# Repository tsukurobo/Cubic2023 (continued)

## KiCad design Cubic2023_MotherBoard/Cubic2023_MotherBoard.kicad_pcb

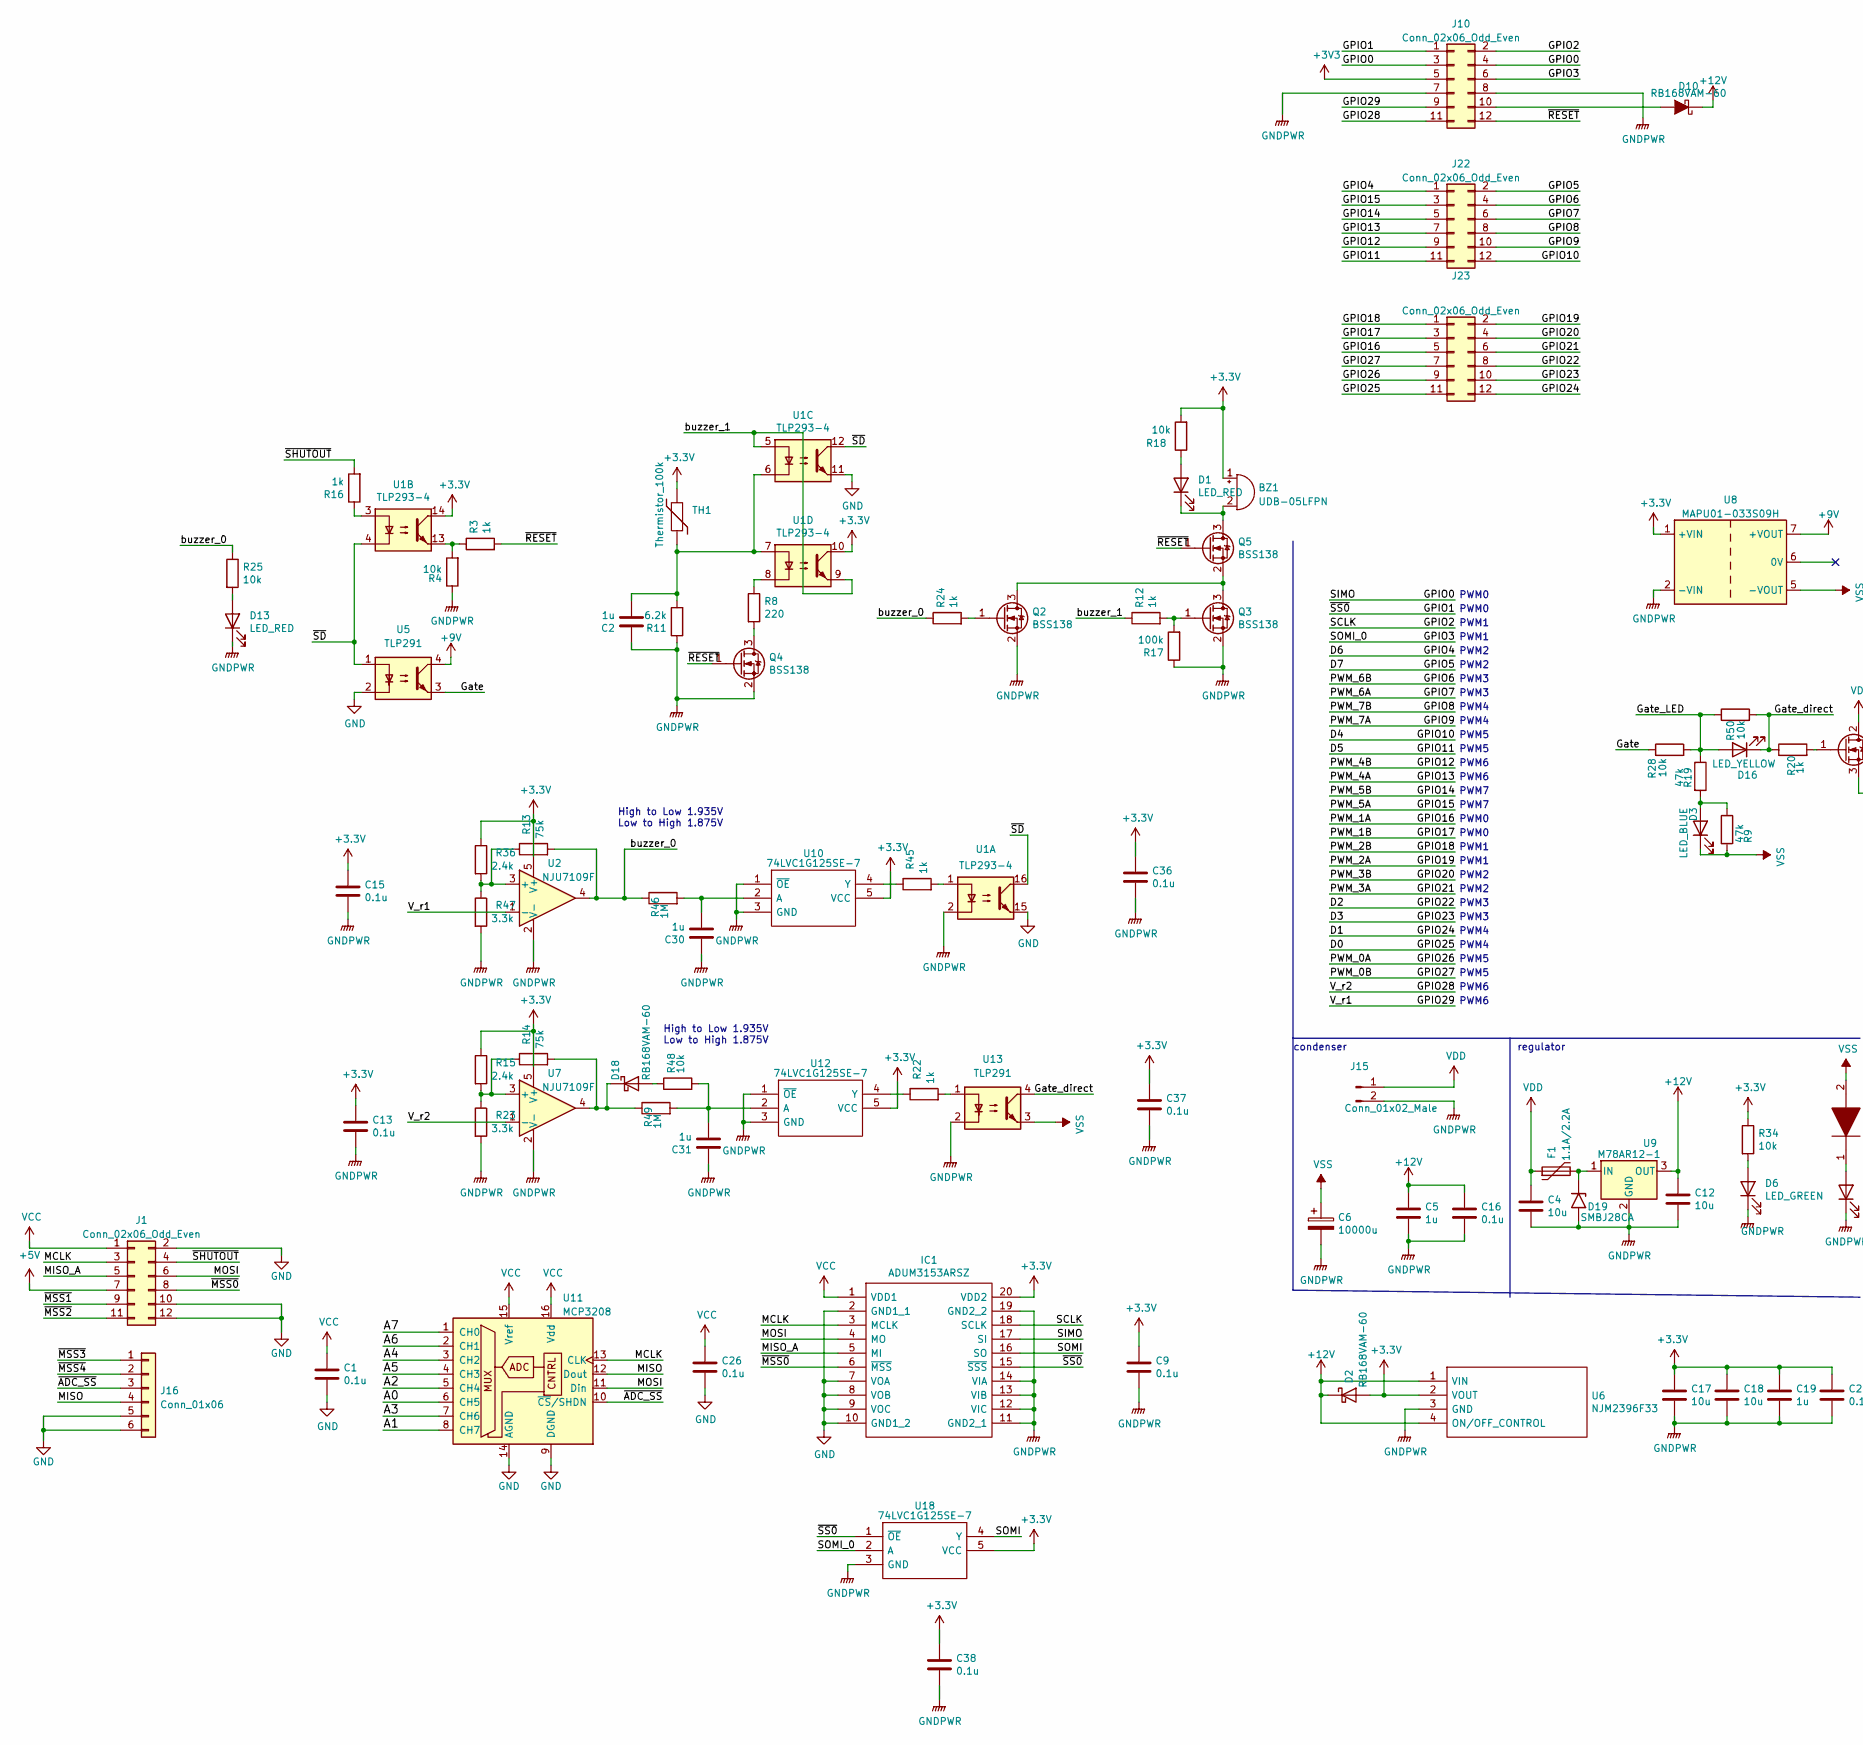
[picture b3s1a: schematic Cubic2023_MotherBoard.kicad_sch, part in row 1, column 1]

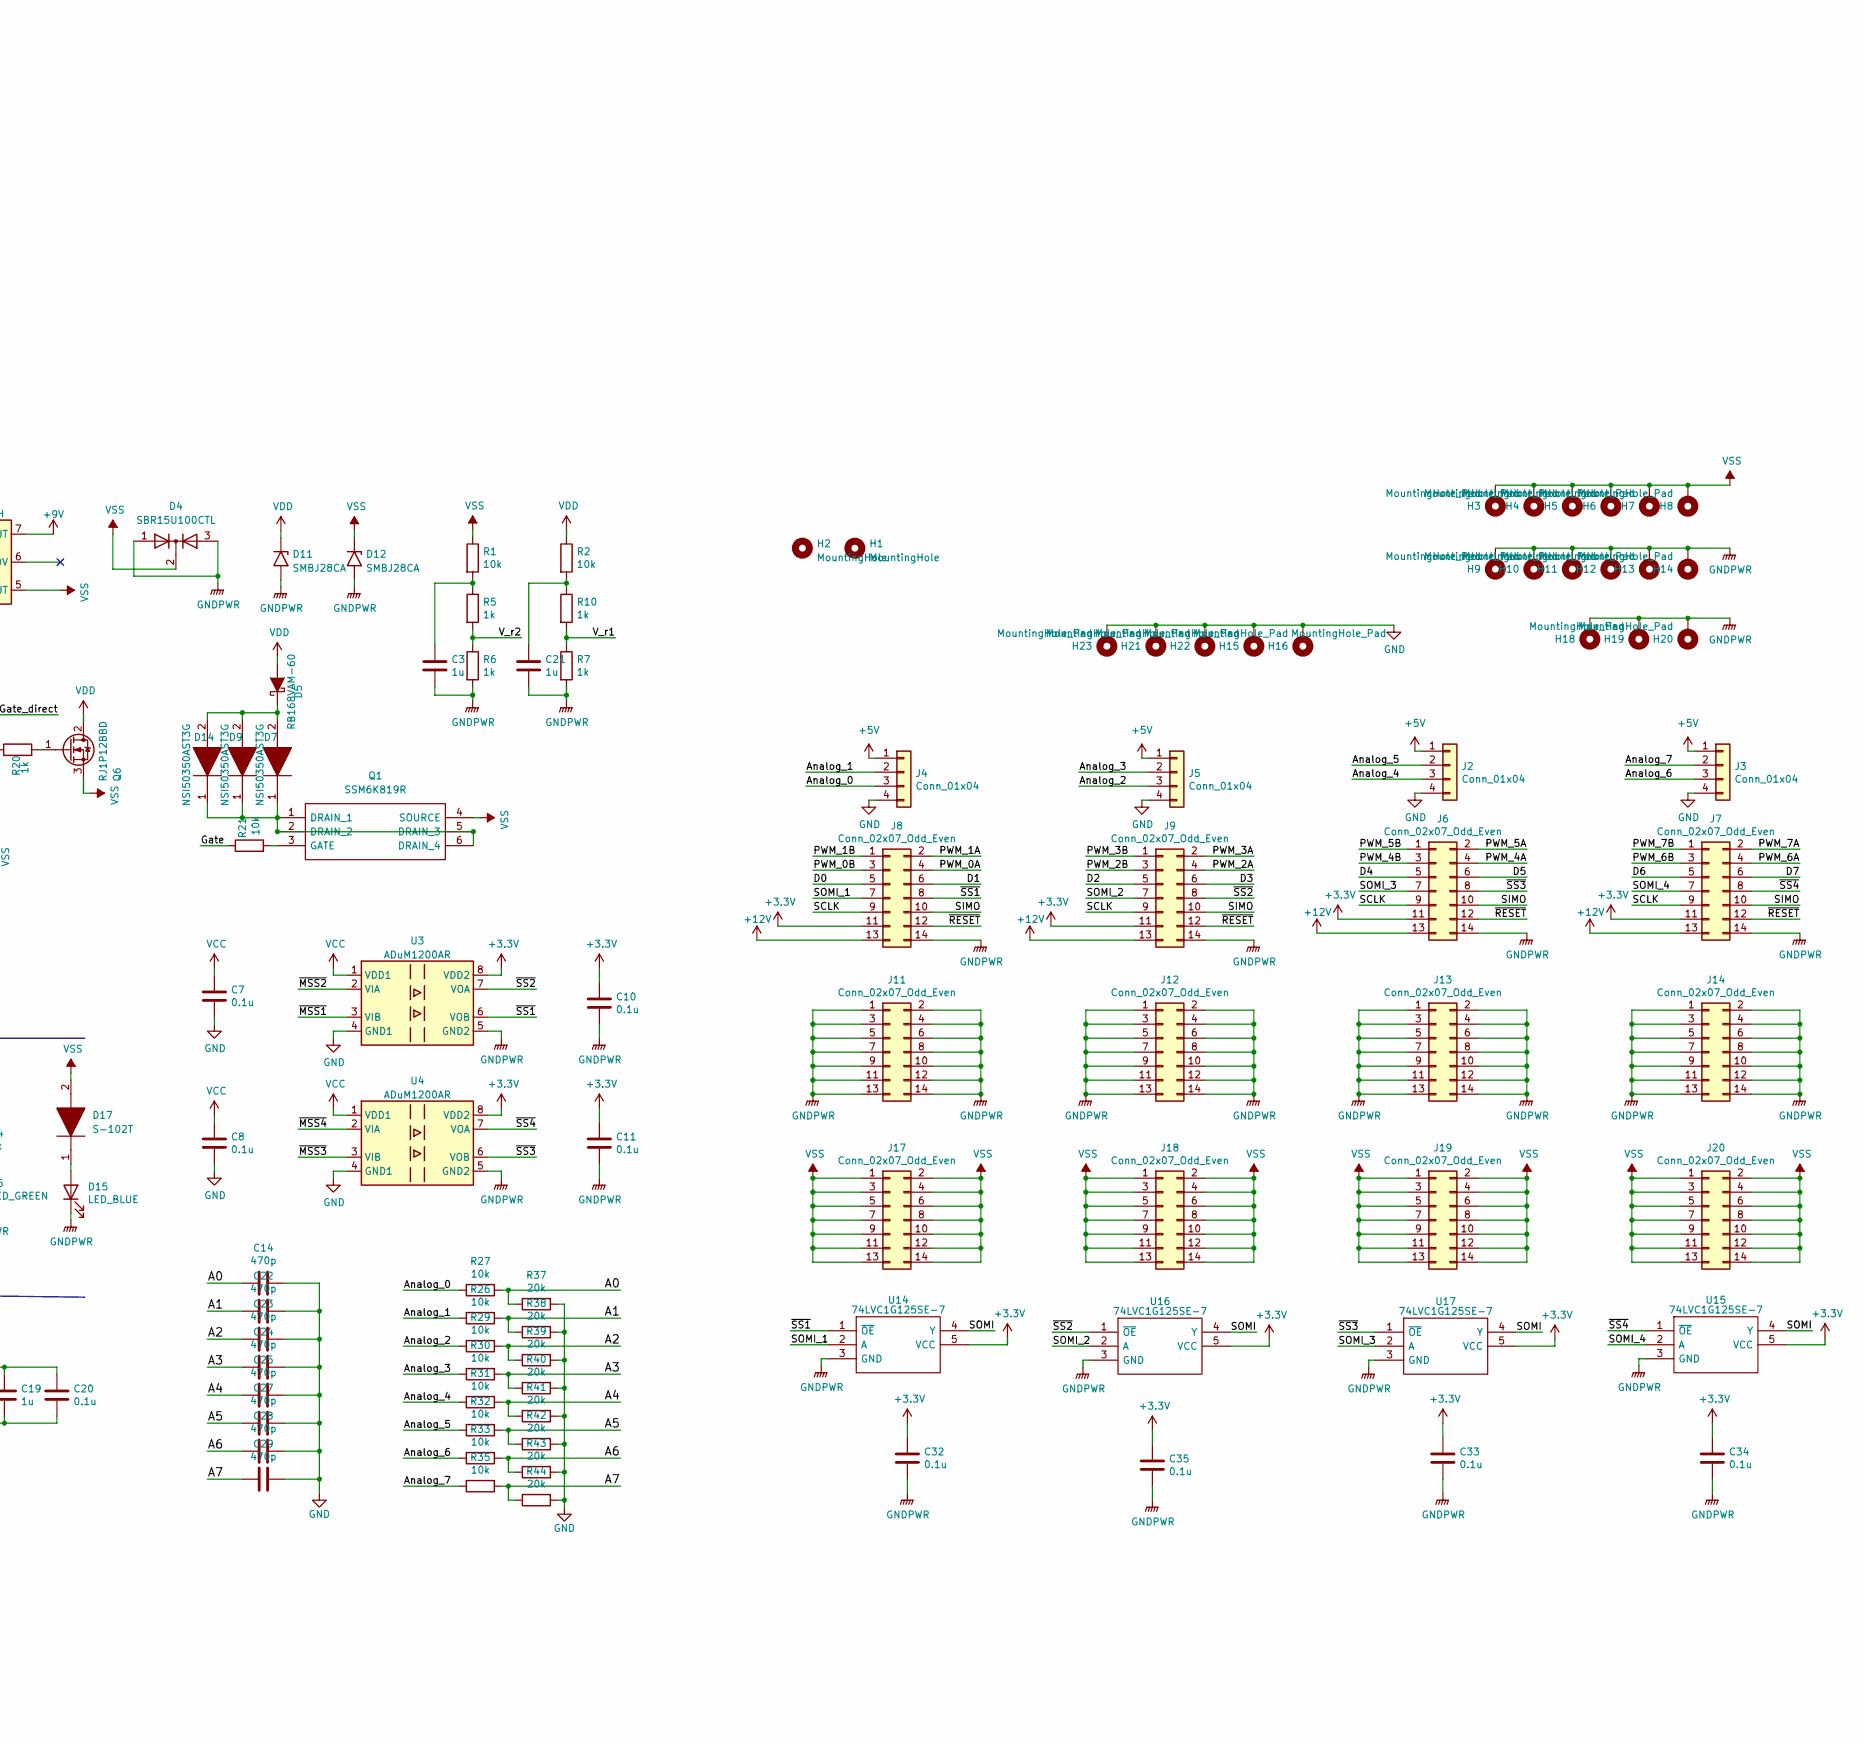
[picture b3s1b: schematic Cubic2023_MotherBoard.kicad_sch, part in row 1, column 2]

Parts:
BZ1: UDB-05LFPN; Buzzer_12x9.5RM7.6
C1, C7, C8, C9, C10, C11, C13, C15, C16, C20, C26, C32, C33, C34, C35, C36, C37, C38: 0.1u; C_0402_1005Metric_Pad0.74x0.62mm_HandSolder; LCSC C307331
C2, C3, C5, C19, C21, C30, C31: 1u; C_0603_1608Metric; LCSC C15849
C4, C12, C17, C18: 10u; C_1206_3216Metric; LCSC C13585
C6: 10000u; CP_Radial_D25.0mm_P10.00mm_SnapIn
C14, C22, C23, C24, C25, C27, C28, C29: 470p; C_0603_1608Metric; LCSC C1620
D1, D13: LED_RED; LED_0603_1608Metric_Pad1.05x0.95mm_HandSolder; LCSC C2286
D2, D5, D10, D18: RB168VAM-60; CUHS20S40H3F
D3, D15: LED_BLUE; LED_0603_1608Metric_Pad1.05x0.95mm_HandSolder; LCSC C72041
D4: SBR15U100CTL; TO-252-2
D6: LED_GREEN; LED_0603_1608Metric_Pad1.05x0.95mm_HandSolder; LCSC C72043
D7, D9, D14: NSI50350AST3G; DIOM7958X256N; Manufacturer_Part_Number NSI50350AST3G; Mouser Part Number 863-NSI50350AST3G
D11, D12, D19: SMBJ28CA; D_SMB
D16: LED_YELLOW; LED_0603_1608Metric_Pad1.05x0.95mm_HandSolder; LCSC C72038
D17: S-102T; SODFL3516X70N; Manufacturer_Part_Number S-102T; Mouser Part Number 954-S-102T
F1: 1.1A/2.2A; Fuse_BelFuse_0ZRE0016FF_L9.9mm_W3.8mm
H1, H2: MountingHole; MountingHole_3.2mm_M3
H3, H4, H5, H6, H7, H8, H9, H10, H11, H12, H13, H14, H15, H16, H18, H19, H20, H21, H22, H23: MountingHole_Pad; MountingHole_2.2mm_M2_DIN965_Pad
IC1: ADUM3153ARSZ; ADUM3153; Manufacturer_Part_Number ADUM3153ARSZ; Mouser Part Number 584-ADUM3153ARSZ
J1: Conn_02x06_Odd_Even; PinSocket_2x06_P2.54mm_Vertical
J2, J3, J4, J5: Conn_01x04; PinSocket_1x04_P2.54mm_Vertical
J6, J7, J8, J9, J11, J12, J13, J14, J17, J18, J19, J20: Conn_02x07_Odd_Even; PinSocket_2x07_P2.54mm_Vertical
J10, J22, J23: Conn_02x06_Odd_Even; PinHeader_2x06_P1.27mm_Vertical
J15: Conn_01x02_Male; T_plug_male_diagonal
J16: Conn_01x06; PinSocket_1x06_P2.54mm_Vertical
Q1: SSM6K819R; SOTFL95P280X88-6N; Manufacturer_Part_Number SSM6K819R; Mouser Part Number N/A
Q2, Q3, Q4, Q5: BSS138; SOT-23
Q6: RJ1P12BBD; TO-263-2
R1, R2, R4, R18, R21, R25, R26, R27, R28, R29, R30, R31, R32, R33, R34, R35, R48, R50: 10k; R_0603_1608Metric; LCSC C25804
R3, R5, R6, R7, R10, R12, R16, R20, R22, R24, R45: 1k; R_0603_1608Metric; LCSC C21190
R8: 220; R_0603_1608Metric; LCSC C22962
R9, R19: 47k; R_0603_1608Metric; LCSC C25819
R11: 6.2k; R_0603_1608Metric; LCSC C25804
R13, R14: 75k; R_0603_1608Metric; LCSC C23242
R15, R36: 2.4k; R_0603_1608Metric; LCSC C22940
R17: 100k; R_0603_1608Metric; LCSC C25803
R23, R47: 3.3k; R_0603_1608Metric; LCSC C22978
R37, R38, R39, R40, R41, R42, R43, R44: 20k; R_0603_1608Metric; LCSC C4184
R46, R49: 1M; R_0603_1608Metric; LCSC C22935
TH1: Thermistor_100k; R_0603_1608Metric
U1: TLP293-4; SO-16_5.3x10.2mm_P1.27mm
U2, U7: NJU7109F; SOT-23-5
U3, U4: ADuM1200AR; SOIC-8_3.9x4.9mm_P1.27mm
U5, U13: TLP291; SOIC-4_4.55x2.6mm_P1.27mm
U6: NJM2396F33; TO-220-4_Horizontal_TabUp; Manufacturer_Part_Number NJM2396F33; Mouser Part Number 513-NJM2396F33
U8: MAPU01-033S09H; MAPU01
U9: M78AR12-1; TO-220-3_Vertical
U10, U12, U14, U15, U16, U17, U18: 74LVC1G125SE-7; SOT-353_SC-70-5; Manufacturer_Part_Number 74LVC1G125SE-7; Mouser Part Number 621-74LVC1G125SE-7
U11: MCP3208; SOIC-16_3.9x9.9mm_P1.27mm

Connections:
+5V: J1.7, J2.1, J3.1, J4.1, J5.1
+9V: U5.4, U8.7 (+VOUT)
+12V: C5.1, C12.1, C16.1, D2.1 (K), D10.1 (K), J6.13, J7.13, J8.13, J9.13, U6.1 (VIN), U6.4 (ON/OFF_CONTROL), U9.3 (OUT)
/A0: C14.1, R27.1, R37.2, U11.6 (CH5)
/A1: C22.1, R26.1, R38.2, U11.8 (CH7)
/A2: C23.1, R29.1, R39.2, U11.5 (CH4)
/A3: C24.1, R30.1, R40.2, U11.7 (CH6)
/A4: C25.1, R31.1, R41.2, U11.3 (CH2)
/A5: C27.1, R32.1, R42.2, U11.4 (CH3)
/A6: C28.1, R33.1, R43.2, U11.2 (CH1)
/A7: C29.1, R35.1, R44.2, U11.1 (CH0)
/Analog_0: J4.3, R27.2
/Analog_1: J4.2, R26.2
/Analog_2: J5.3, R29.2
/Analog_3: J5.2, R30.2
/Analog_4: J2.3, R31.2
/Analog_5: J2.2, R32.2
/Analog_6: J3.3, R33.2
/Analog_7: J3.2, R35.2
/D0: J8.5, J23.11
/D1: J8.6, J23.12
/D2: J9.5, J23.8
/D3: J9.6, J23.10
/D4: J6.5, J22.12
/D5: J6.6, J22.11
/D6: J7.5, J22.1
/D7: J7.6, J22.2
/GPIO0: IC1.17 (SI), J6.10, J7.10, J8.10, J9.10, J10.3, J10.4
/GPIO1: IC1.15 (~SSS), J10.1, U18.1 (~OE)
/GPIO2: IC1.18 (SCLK), J6.9, J7.9, J8.9, J9.9, J10.2
/GPIO3: J10.6, U18.2 (A)
/GPIO6: J7.3, J22.4
/GPIO7: J7.4, J22.6
/GPIO8: J7.1, J22.8
/GPIO9: J7.2, J22.10
/GPIO12: J6.3, J22.9
/GPIO13: J6.4, J22.7
/GPIO14: J6.1, J22.5
/GPIO15: J6.2, J22.3
/GPIO16: J8.2, J23.5
/GPIO17: J8.1, J23.3
/GPIO18: J9.3, J23.1
/GPIO19: J9.4, J23.2
/GPIO20: J9.1, J23.4
/GPIO21: J9.2, J23.6
/GPIO26: J8.4, J23.9
/GPIO27: J8.3, J23.7
/GPIO28: J10.11, R5.2, R6.1, U7.1 (-)
/GPIO29: J10.9, R7.1, R10.2, U2.1 (-)
/Gate: R21.1, R28.1, U5.3
/Gate_LED: D16.2 (A), R19.1, R28.2, R50.1
/Gate_direct: D16.1 (K), R20.1, R50.2, U13.4
/MCLK: IC1.3 (MCLK), J1.3, U11.13 (CLK)
/MISO: J16.4, U11.12 (Dout)
/MISO_A: IC1.5 (MI), J1.5
/MOSI: IC1.4 (MO), J1.6, U11.11 (Din)
/SOMI: IC1.16 (SO), U14.4 (Y), U15.4 (Y), U16.4 (Y), U17.4 (Y), U18.4 (Y)
/SOMI_1: J8.7, U14.2 (A)
/SOMI_2: J9.7, U16.2 (A)
/SOMI_3: J6.7, U17.2 (A)
/SOMI_4: J7.7, U15.2 (A)
/buzzer_0: R13.2, R24.1, R25.1, R46.1, U2.4
/buzzer_1: R12.1, U1.5, U1.9
/~ADC_SS: J16.3, U11.10 (~CS/SHDN)
/~MSS0: IC1.6 (~MSS), J1.8
/~MSS1: J1.9, U3.3 (VIB)
/~MSS2: J1.11, U3.2 (VIA)
/~MSS3: J16.1, U4.3 (VIB)
/~MSS4: J16.2, U4.2 (VIA)
/~RESET: J6.12, J7.12, J8.12, J9.12, J10.12, Q4.1 (G), Q5.1 (G), R3.2
/~SD: U1.4, U1.12, U1.16, U5.1
/~SHUTOUT: J1.4, R16.2
/~SS1: J8.8, U3.6 (VOB), U14.1 (~OE)
/~SS2: J9.8, U3.7 (VOA), U16.1 (~OE)
/~SS3: J6.8, U4.6 (VOB), U17.1 (~OE)
/~SS4: J7.8, U4.7 (VOA), U15.1 (~OE)
GND: C1.2, C7.2, C8.2, C14.2, C22.2, C23.2, C24.2, C25.2, C26.2, C27.2, C28.2, C29.2, H15.1, H16.1, H21.1, H22.1, H23.1, IC1.2 (GND1_1), IC1.7 (VOA), IC1.8 (VOB), IC1.9 (VOC), IC1.10 (GND1_2), J1.2, J1.10, J1.12, J2.4, J3.4, J4.4, J5.4, J16.5, J16.6, R37.1, R38.1, R39.1, R40.1, R41.1, R42.1, R43.1, R44.1, U1.11, U1.15, U3.4 (GND1), U4.4 (GND1), U5.2, U11.9 (DGND), U11.14 (AGND)
GNDPWR: C2.1, C3.2, C4.2, C5.2, C6.2, C9.2, C10.2, C11.2, C12.2, C13.2, C15.2, C16.2, C17.2, C18.2, C19.2, C20.2, C21.2, C30.1, C31.1, C32.2, C33.2, C34.2, C35.2, C36.2, C37.2, C38.2, D4.1 (A), D4.3 (A), D6.1 (K), D11.2 (A2), D12.2 (A2), D13.1 (K), D15.1 (K), D19.2 (A2), H9.1, H10.1, H11.1, H12.1, H13.1, H14.1, H18.1, H19.1, H20.1, IC1.11 (GND2_1), IC1.12 (VIC), IC1.13 (VIB), IC1.14 (VIA), IC1.19 (GND2_2), J6.14, J7.14, J8.14, J9.14, J10.7, J10.8, J11.1, J11.2, J11.3, J11.4, J11.5, J11.6, J11.7, J11.8, J11.9, J11.10, J11.11, J11.12, J11.13, J11.14, J12.1, J12.2, J12.3, J12.4, J12.5, J12.6, J12.7, J12.8, J12.9, J12.10, J12.11, J12.12, J12.13, J12.14, J13.1, J13.2, J13.3, J13.4, J13.5, J13.6, J13.7, J13.8, J13.9, J13.10, J13.11, J13.12, J13.13, J13.14, J14.1, J14.2, J14.3, J14.4, J14.5, J14.6, J14.7, J14.8, J14.9, J14.10, J14.11, J14.12, J14.13, J14.14, J15.2, Q2.2 (S), Q3.2 (S), Q4.2 (S), R4.1, R6.2, R7.2, R11.1, R17.1, R23.2, R47.2, U1.2, U2.2 (V-), U3.5 (GND2), U4.5 (GND2), U6.3 (GND), U7.2 (V-), U8.2 (-VIN), U9.2 (GND), U10.1 (~OE), U10.3 (GND), U12.1 (~OE), U12.3 (GND), U13.2, U14.3 (GND), U15.3 (GND), U16.3 (GND), U17.3 (GND), U18.3 (GND)
unnamed: BZ1.2 (+), D1.1 (K), Q5.3 (D)
unnamed: C2.2, R11.2, TH1.1, U1.6, U1.7
unnamed: C3.1, R1.2, R5.1
unnamed: C21.1, R2.2, R10.1
unnamed: C30.2, R46.2, U10.2 (A)
unnamed: C31.2, R48.2, R49.2, U12.2 (A)
unnamed: D1.2 (A), R18.1
unnamed: D3.2 (A), R9.1, R19.2
unnamed: D6.2 (A), R34.2
unnamed: D10.2 (A), J10.10
unnamed: D13.2 (A), R25.2
unnamed: D7.1, D9.1, D14.1, Q1.1 (DRAIN_1), Q1.2 (DRAIN_2), Q1.5 (DRAIN_3), Q1.6 (DRAIN_4)
unnamed: D5.1 (K), D7.2, D9.2, D14.2
unnamed: D15.2 (A), D17.1
unnamed: D18.1 (K), R14.2, R49.1, U7.4
unnamed: D18.2 (A), R48.1
unnamed: D19.1 (A1), F1.2, U9.1 (IN)
unnamed: Q1.3 (GATE), R21.2
unnamed: Q2.1 (G), R24.2
unnamed: Q2.3 (D), Q3.3 (D), Q5.2 (S)
unnamed: Q3.1 (G), R12.2, R17.2
unnamed: Q4.3 (D), R8.2
unnamed: Q6.1 (G), R20.2
unnamed: R3.1, R4.2, U1.13
unnamed: R8.1, U1.8
unnamed: R13.1, R36.2, R47.1, U2.3 (+)
unnamed: R14.1, R15.2, R23.1, U7.3 (+)
unnamed: R16.1, U1.3
unnamed: R22.1, U12.4 (Y)
unnamed: R22.2, U13.1
unnamed: R45.1, U10.4 (Y)
unnamed: R45.2, U1.1
VCC: C1.1, C7.1, C8.1, C26.1, IC1.1 (VDD1), J1.1, U3.1 (VDD1), U4.1 (VDD1), U11.15 (Vref), U11.16 (Vdd)
VDD: C4.1, D5.2 (A), D11.1 (A1), F1.1, J15.1, Q6.2 (D), R2.1
VSS: C6.1, D3.1 (K), D4.2 (K), D12.1 (A1), D17.2, H3.1, H4.1, H5.1, H6.1, H7.1, H8.1, J17.1, J17.2, J17.3, J17.4, J17.5, J17.6, J17.7, J17.8, J17.9, J17.10, J17.11, J17.12, J17.13, J17.14, J18.1, J18.2, J18.3, J18.4, J18.5, J18.6, J18.7, J18.8, J18.9, J18.10, J18.11, J18.12, J18.13, J18.14, J19.1, J19.2, J19.3, J19.4, J19.5, J19.6, J19.7, J19.8, J19.9, J19.10, J19.11, J19.12, J19.13, J19.14, J20.1, J20.2, J20.3, J20.4, J20.5, J20.6, J20.7, J20.8, J20.9, J20.10, J20.11, J20.12, J20.13, J20.14, Q1.4 (SOURCE), Q6.3 (S), R1.1, R9.2, U8.5 (-VOUT), U13.3

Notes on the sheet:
High to Low 1.935V Low to High 1.875V
PWM6
PWM2
PWM0
PWM1
PWM4
PWM5
PWM7
PWM3
regulator
condenser

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
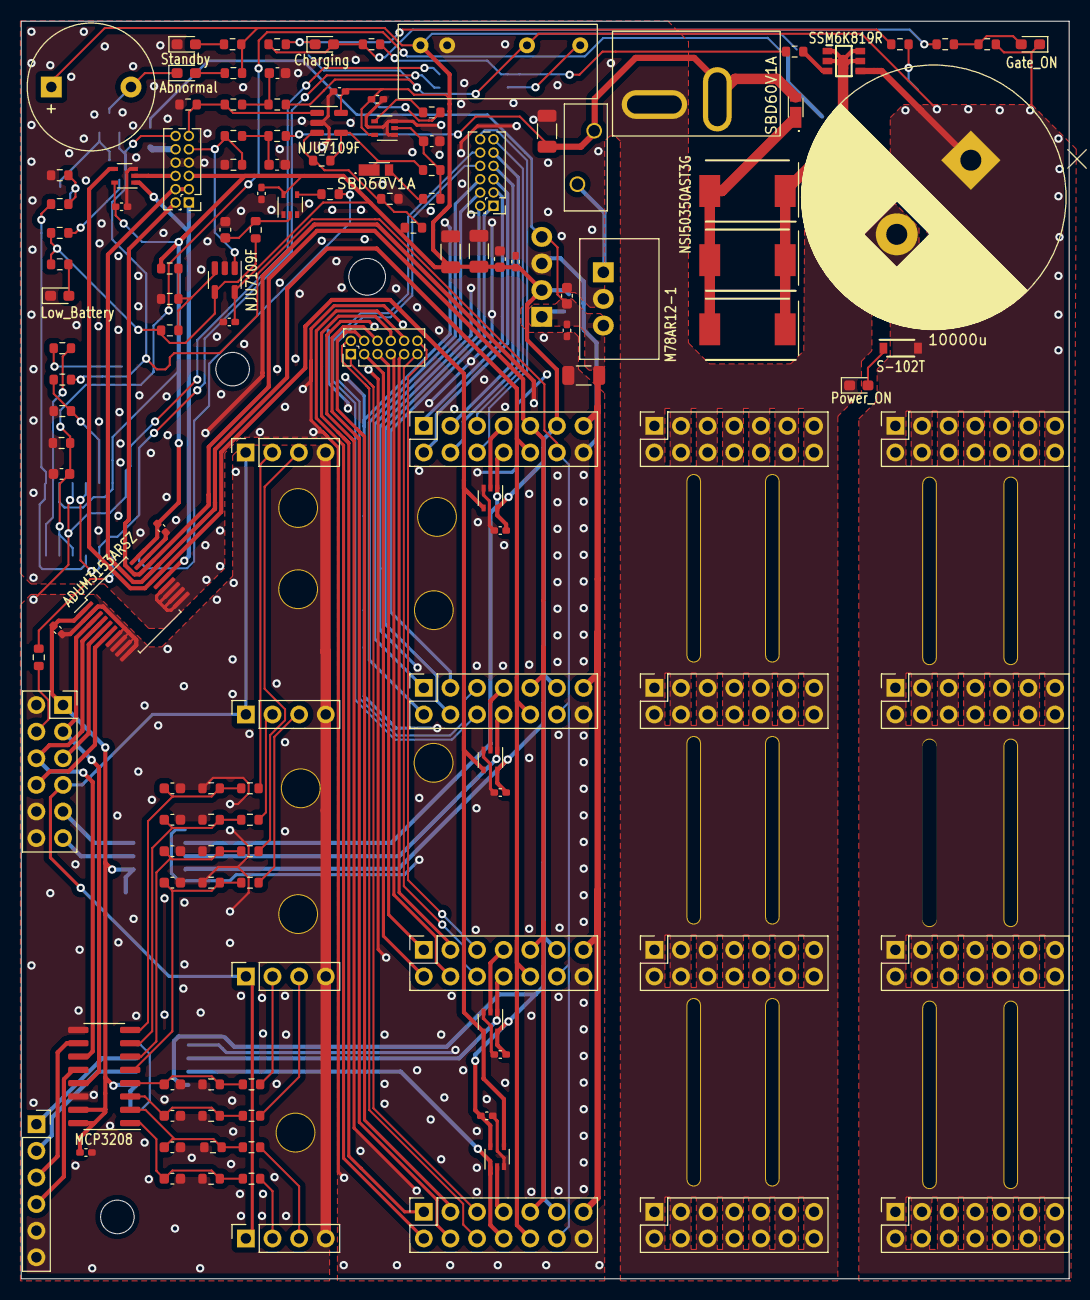
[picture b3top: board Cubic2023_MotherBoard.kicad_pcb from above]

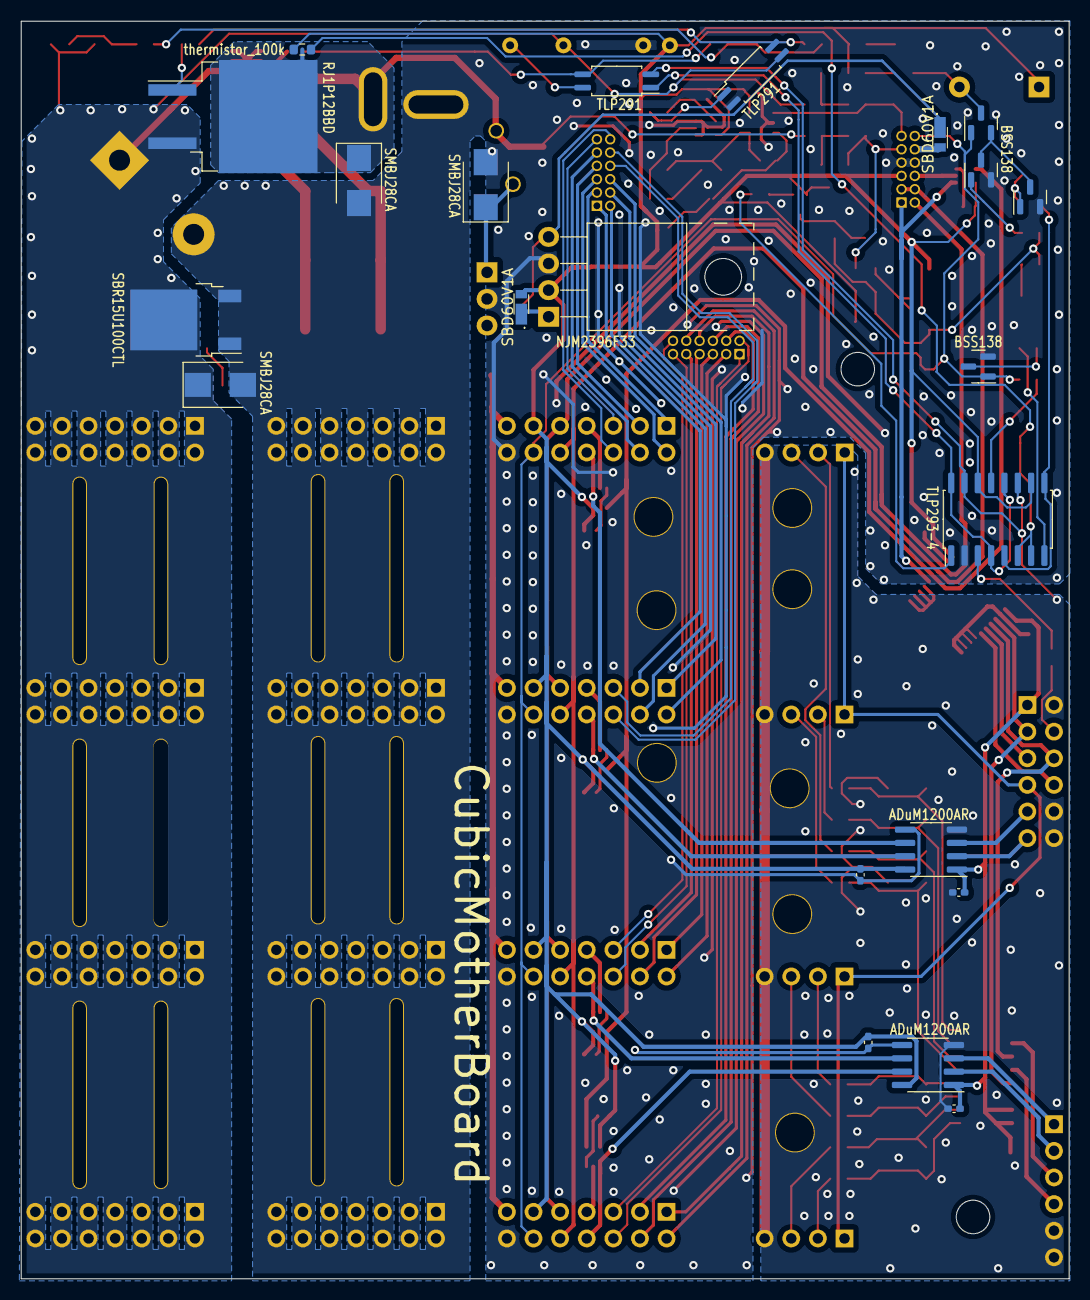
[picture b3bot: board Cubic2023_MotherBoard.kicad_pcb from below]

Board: 2 copper layers, 100.0 x 120.0 mm, 178 parts (22 on the bottom side), 114 nets.
